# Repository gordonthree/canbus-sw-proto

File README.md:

# CAN bus switch prototype

Some circuit board sketches in the free version of EagleCad

## Brain board
* Raspberry Pi 3 or 4?
* Touchscreen usb + hdmi
* CAN bus to SPI shield
* Web based interface

## Alt brain board
* 1x ESP32
* 1x CAN bus transciever
* 1x 4-pos screw terminal for power + can
* 

## Demo 01 - Single switch with STM32 and CANBUS
* <br>
* 1x STM32F042
* 1x Isolated CAN bus transciever
* 1x Infineon BTS50010-1TAD PROFet Smart High Side Switch
* Voltage monitoring via resistor divider
* Current monitoring via Smart Switch
* Onboard 3v3 and 5v linear regulators
* Headers for SWLINK and UART
* Wago style screw terminal connector for 2-wire + drain CANBUS cable
* High current terminal block style battery input and load output
  
## Demo 02 - Single switch 
* 1x Infineon BTS50010-1TAD PROFet Smart High Side Switch
* Voltage monitoring via resistor divider
* Current monitoring via Smart Switch
* Header for control connection to microcontroller
* High current terminal block style battery input and load output

## Demo 03 - Dual switch with STM32 and CANBUS
* 1x STM32F042
* 1x Isolated CAN bus transciever
* 2x Infineon BTS50010-1TAD PROFet Smart High Side Switch
* Voltage monitoring via resistor divider
* Current monitoring via Smart Switch
* Onboard 3v3 and 5v linear regulators
* Headers for SWLINK and UART
* Wago style screw terminal connector for 2-wire + drain CANBUS cable
* High current terminal block style battery input and load output
  
## Prototype 01 Four switches
* 1x ESP32
* 1x CAN bus transciever
* 2x p-channel FETs (20a max?)
* 2x high side switch ICs (10a max?)
* 1x dual chan driver TC4472
* 1x 6-pos barrier strip V+ GND SW1 SW2 SW3 SW4
* 1x 3-pos terminal for can bus
* 1x serial programming header

## Prototype 02 Three switches
* 1x ESP32
* 1x CAN bus transciever
* 2x p-channel FETs (30a max?) power-so8
* 1x high side switch ICs (10a max?)
* 1x dual chan driver TC4472
* 1x 6-pos barrier strip V+ V+ SW1 SW2 SW3 GND
* 1x 3-pos terminal for can bus
* 1x serial programming header
  
## Prototype 03 Six switch
* 1x ESP32
* 1x CAN bus transciever
* 4x p-channel FETs (30a max?) power-so8
* 2x high side switch ICs (10a max?)
* 1x dual chan driver TC4472
* 1x 3-pos barrier strip for power +12 +12 GND
* 2x 6-pos barrier strip SW1 GND SW2 GND SW3 GND - repeated for other side
* 1x 3-pos terminal for can bus
* 1x serial programming header

## Prototype 04 Three switches with STM32
* 1x STM32F042C6
* 1x CAN bus transciever
* 2x p-channel FETs (30a max?) power-so8
* 1x high side switch ICs (10a max?)
* 1x dual chan driver TC4472
* 1x 6-pos barrier strip V+ V+ SW1 SW2 SW3 GND
* 1x 3-pos terminal for can bus
* 1x serial programming header
 
## Minimum interconnect for nodes
* 2-pair cable with drain
* first pair for CANH-IN and CANL-IN
* second pair for CANH-OUT and CANL-OUT
* drain is grounded at controller / hub

## Ideal interconnect for nodes
* 4-pair cable with drain
* first pair for CANH-IN and CANL-IN
* second and fourth pair for +VBAT and ground
* third pair for CANH-OUT and CANL-OUT
* drain is grounded at controller / hub

## CAN Hub
* eight total de9 connectors, one input, one output, six spurs
* each spur is wired in series, with Cx-IN and Cx-OUT daisy chained
* spurs that are not connected have a shorting plug installed connecting Cx-IN to Cx-OUT

## Parts
* 4x8 RGB matrix keypad https://www.adafruit.com/product/4020
* high side switch (ssr) https://mou.sr/4jcK616
* 6 position terminal block https://mou.sr/4i4P92Y
* heavy duty 6-pos terminal https://mou.sr/3R63QYn
* heavy duty 3-pos terminal block https://mou.sr/3FTFHBW
* ATO fuse holder https://mou.sr/4cihwsZ
* CANBUS Transceiver MCP2562T https://mou.sr/4llTLVa 
* ESP32 Module https://mou.sr/4j1XWDP
* Onboard DC-DC converter https://mou.sr/4i8eVTN
* P chan fet chonky https://mou.sr/42aUOja
* P chan power-so8 https://mou.sr/42BhcBs
* 3.3v LDO regulator https://mou.sr/3RgIUy6
* 20 awg shielded twisted pair cable https://a.co/d/8FQRYBL
* Texas Inst mosfet driver 5a inverted dual-ch SO8 https://mou.sr/3YqDYuk
* STM32 Micro with CAN bus 20 pin ssop https://mou.sr/4jwf9Fx
* ESP32 WROOM module with antenna https://mou.sr/3XWw2kl
* STM32 Dev Board using inexepensive mcu https://www.digikey.com/short/59jq87v5
* STM32 48-pin QFP STM32F042C6T7 https://mou.sr/3Eqjfjx
* DC-DC Switching regulator TPS560430 automotive 5v output https://mou.sr/4cZ1YLn
* DC-DC Sync-switching regulator LMR51625 automotive adjustable output https://mou.sr/4ipTHB4

## remote node introductions
* 10 seconds after boot remote nodes will start sending introduction messages 0x7XX
  * master will record message id and node id for each device
  * master will compare node id with database of known nodes
  * nodes that are already known will have their last-seen timestamp updated
  * newly introduced nodes will be added to the database, recording their first-seen timestamp
  * master will respond with 0x401 to the node to acknowledge introduction
  * after reciving 0x401 the remote node will clear the introduction flag and enter normal operation
* after no introductions the master will enumerate new nodes
  * master will send 0x402:0x40A to the remote node and nodes will respond with 0x710:0x74F for each module the node offers
  * modules will be recorded in database using unique 32-bit node ID and 16-bit module ID
  * master will send 0x401 to the remote node after recording each module 
* after introductions and enumeration master will review database of nodes
  * nodes with a timestamp older than the current boot timestamp will be marked as not-present
    * master will send 0x40C node check message to the node
    * if remote node responds with their node id, update last seen, flag for enumeration 
    * if remote node does not respond mark the node missing in the database and alert user

## normal operation
* after introduction and enumeration are complete master will send 0x10A indicating nodes should begin normal operation
* nodes start sending 0x5XX data messages at the configured rates

## request info flag
* master will instruct display module to request info, providing a message id
* display module will watch for the message id and receive 8 bytes of data

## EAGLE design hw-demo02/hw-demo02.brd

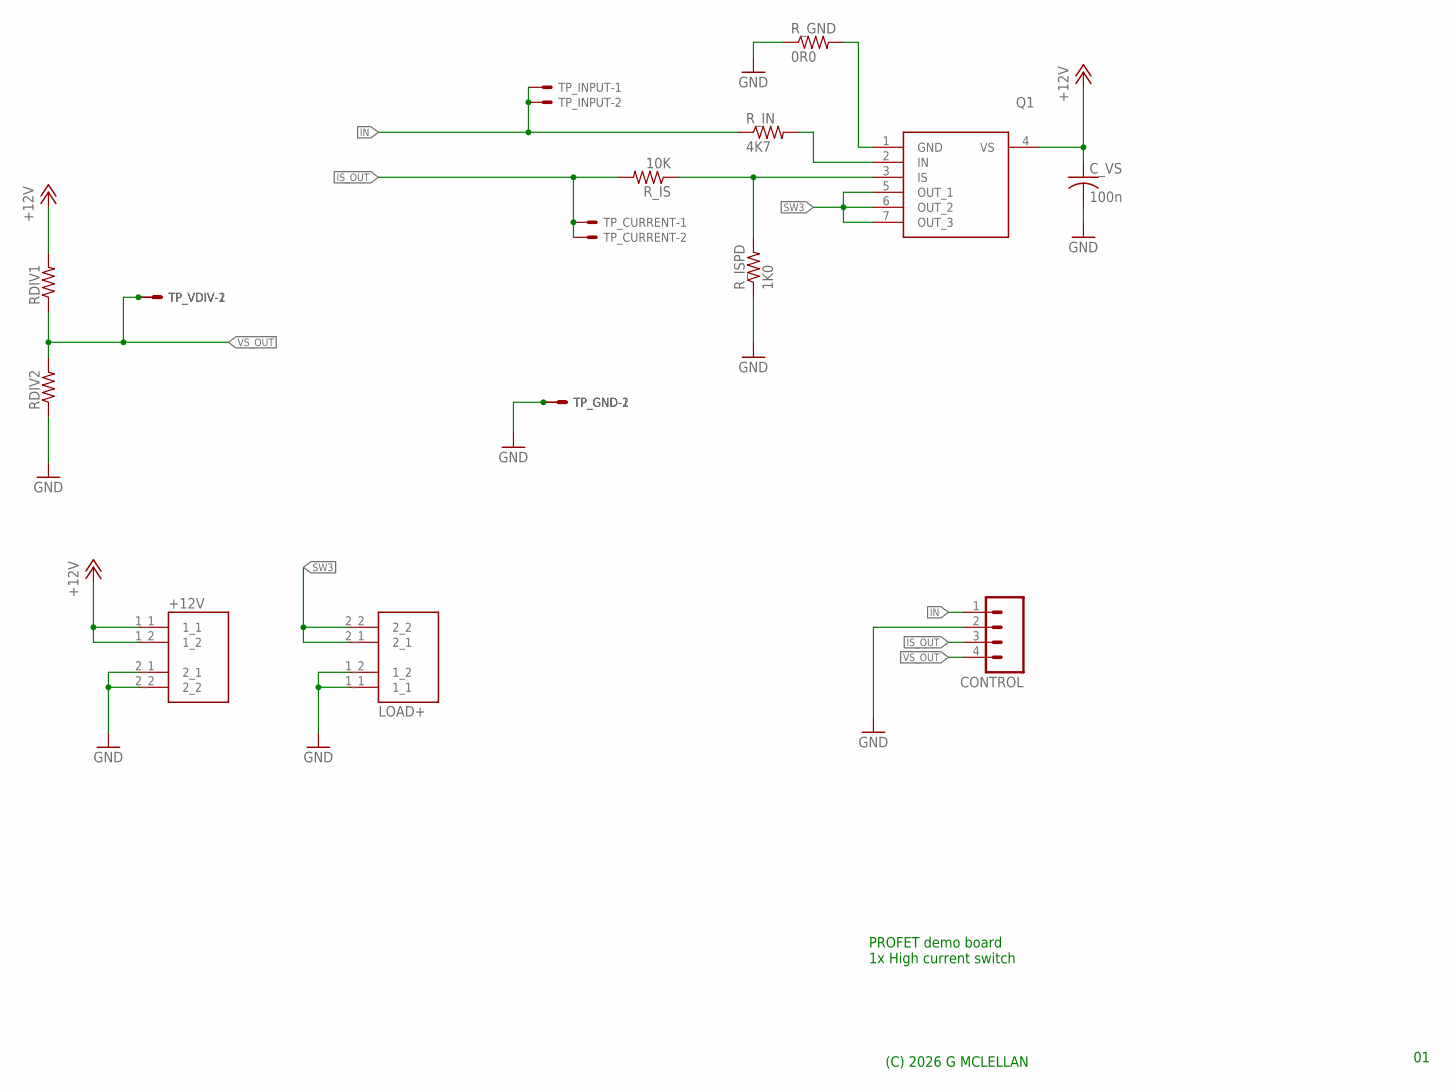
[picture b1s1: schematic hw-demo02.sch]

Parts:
+12V: VP0265840000G; AMPHENOL_VP0265840000G
CONTROL: M04LOCK; 1X04_LOCK
C_VS: 100n; C0805K
LOAD+: VP0265840000G; AMPHENOL_VP0265840000G
Q1: BTS500101TADATMA2
RDIV1, RDIV2: R-US_R0805; R0805
R_GND: 0R0; R1206W
R_IN: 4K7; 0207/12
R_IS: 10K; 0207/12
R_ISPD: 1K0; 0207/12
TP_CURRENT: 22-23-2021
TP_GND: 22-23-2021
TP_INPUT: 22-23-2021
TP_VDIV: 22-23-2021

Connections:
+12V: +12V.1_1, +12V.1_2, C_VS.1, Q1.4 (VS), RDIV1.2
CTL3`: Q1.2 (IN), R_IN.2
GND: +12V.2_1, +12V.2_2, CONTROL.2, C_VS.2, LOAD+.1_1, LOAD+.1_2, RDIV2.1, R_GND.1, R_ISPD.1, TP_GND.1, TP_GND.2
IN: CONTROL.1, R_IN.1, TP_INPUT.1, TP_INPUT.2
IS: Q1.3 (IS), R_IS.1, R_ISPD.2
IS_OUT: CONTROL.3, R_IS.2, TP_CURRENT.1, TP_CURRENT.2
unnamed: Q1.1 (GND), R_GND.2
SW3: LOAD+.2_1, LOAD+.2_2, Q1.5 (OUT_1), Q1.6 (OUT_2), Q1.7 (OUT_3)
VS_OUT: CONTROL.4, RDIV1.1, RDIV2.2, TP_VDIV.1, TP_VDIV.2

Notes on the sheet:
PROFET demo board 1x High current switch
(C) 2026 G MCLELLAN

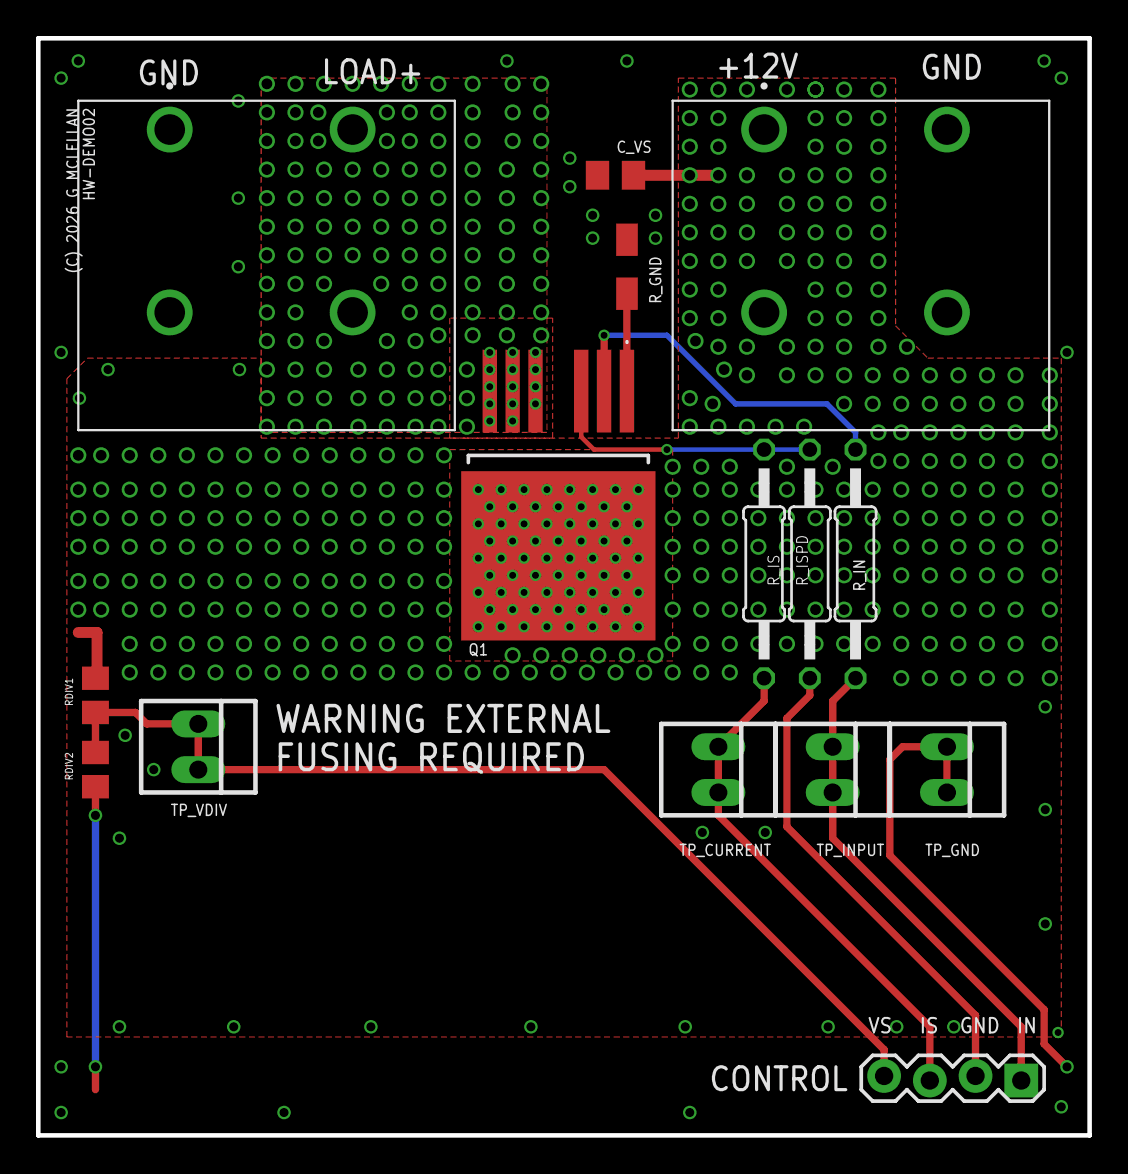
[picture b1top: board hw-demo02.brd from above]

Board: 2 copper layers, 58.4 x 61.0 mm, 15 parts (0 on the bottom side), 9 nets.

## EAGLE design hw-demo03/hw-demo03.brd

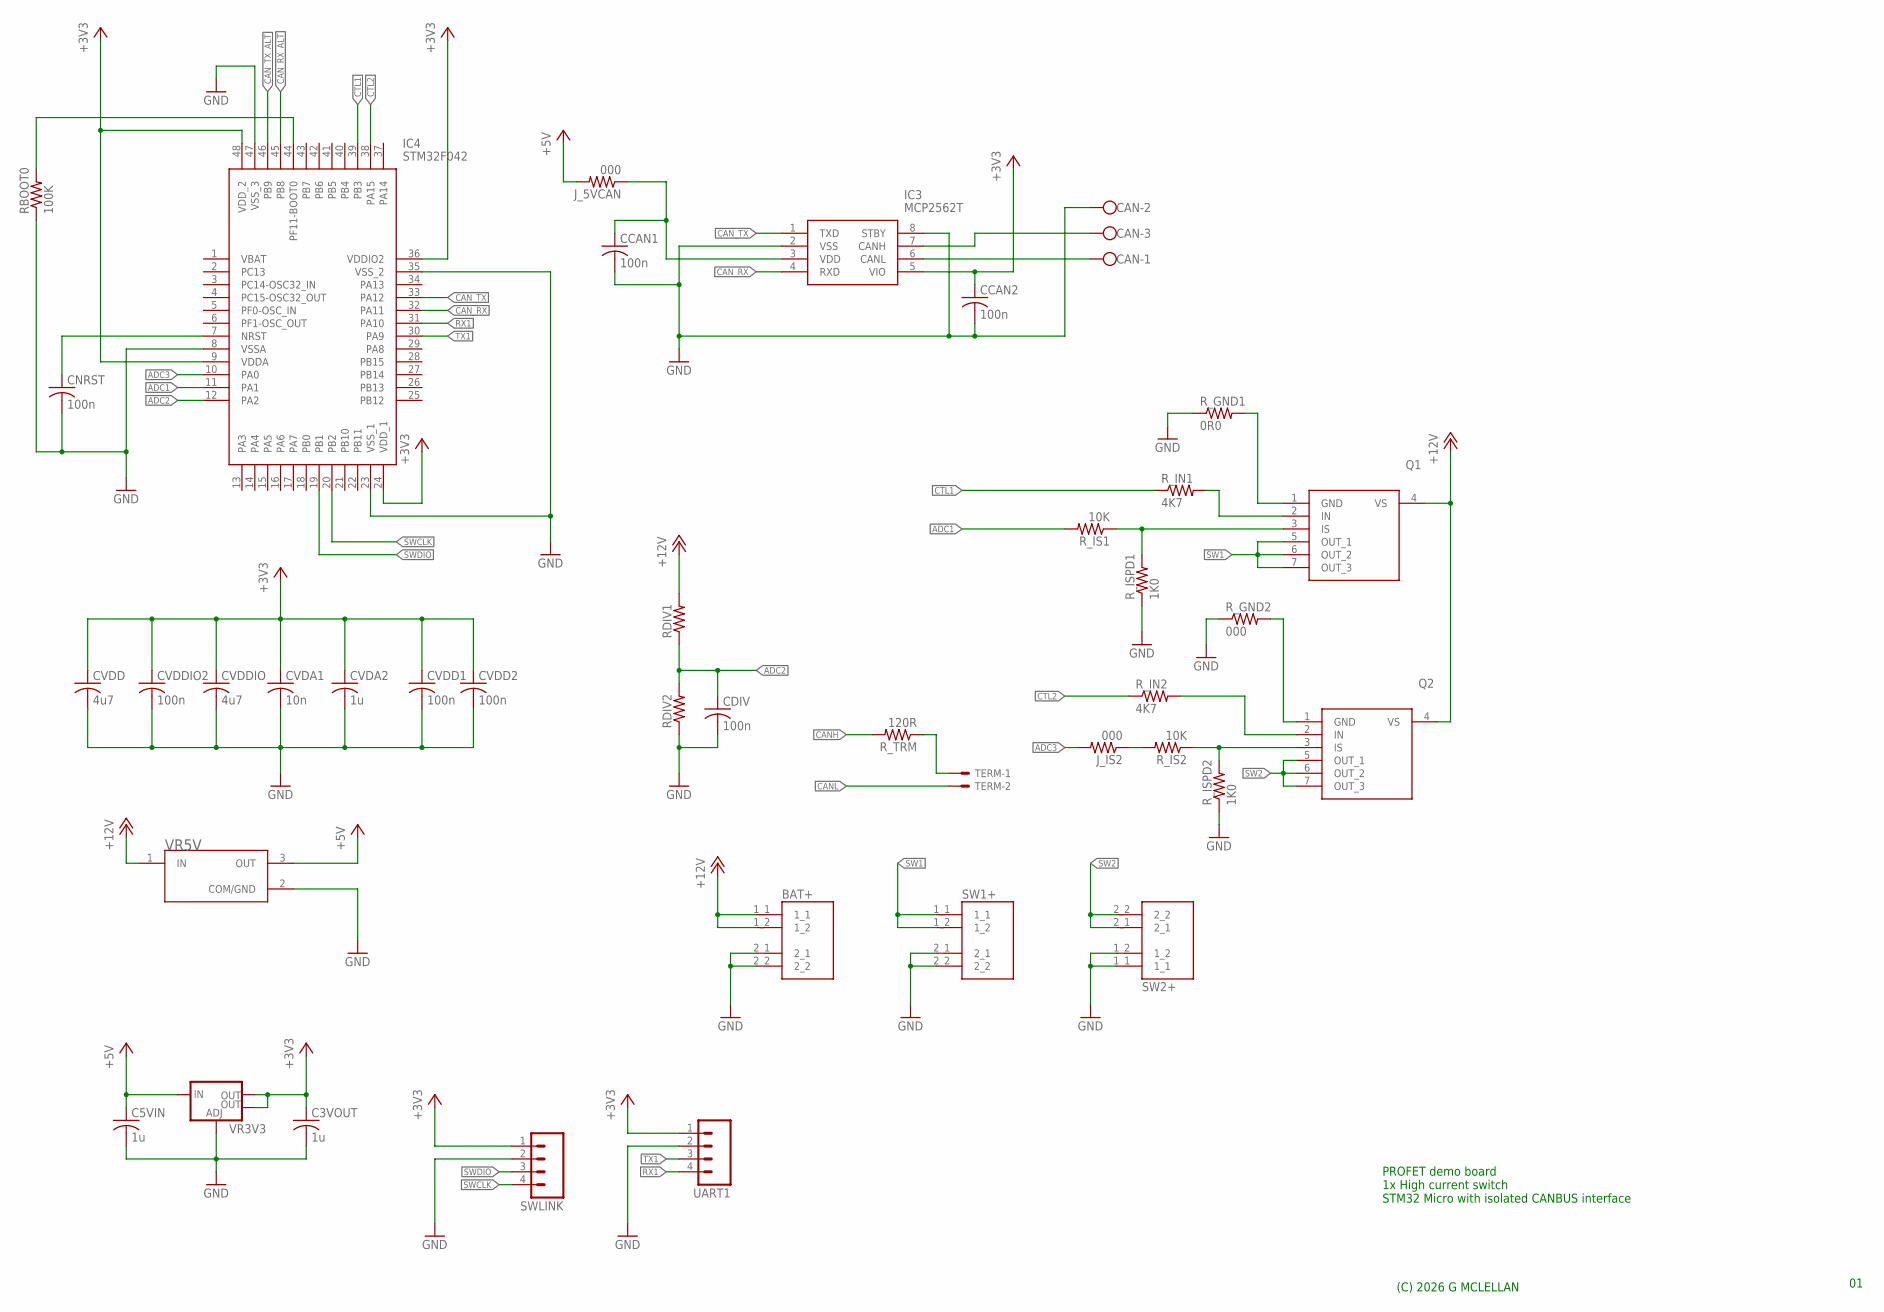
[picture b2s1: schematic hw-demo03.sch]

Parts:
BAT+: VP0265840000G; AMPHENOL_VP0265840000G
C3VOUT: 1u; C0805K
C5VIN: 1u; C1206K
CAN: W237-103
CCAN1, CCAN2: 100n; C0603K
CDIV: 100n; C0603K
CNRST: 100n; C0603K
CVDA1: 10n; C0603K
CVDA2: 1u; C0603K
CVDD: 4u7; C0603K
CVDD1, CVDD2: 100n; C0603K
CVDDIO: 4u7; C0603K
CVDDIO2: 100n; C0603K
IC3: MCP2562T; SOIC127P600X175-8N
IC4: STM32F042; QFP50P900X900X160-48N
J_5VCAN: 000; 0207/15
J_IS2: 000; 0207/15
Q1, Q2: BTS500101TADATMA2
RBOOT0: 100K; R0603
RDIV1, RDIV2: R-US_R0805; R0805
R_GND1: 0R0; R1206W
R_GND2: 000; R1206W
R_IN1: 4K7; 0207/10
R_IN2: 4K7; 0204/7
R_IS1, R_IS2: 10K; 0204/7
R_ISPD1, R_ISPD2: 1K0; 0204/7
R_TRM: 120R; 0204/7
SW1+, SW2+: VP0265840000G; AMPHENOL_VP0265840000G
SWLINK: M04LOCK; 1X04_LOCK
TERM: 22-23-2021
UART1: M04LOCK; 1X04_LOCK
VR3V3: V_REG_LM1117SOT223; SOT223
VR5V: OKI-78SR-5/1.5-W36-C; CONV_OKI-78SR-5/1.5-W36-C

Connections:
+3V3: C3VOUT.1, CCAN2.1, CVDA1.1, CVDA2.1, CVDD.1, CVDD1.1, CVDD2.1, CVDDIO.1, CVDDIO2.1, IC3.5 (VIO), IC4.9 (VDDA), IC4.24 (VDD_1), IC4.36 (VDDIO2), IC4.48 (VDD_2), SWLINK.1, UART1.1, VR3V3.2 (OUT), VR3V3.4 (OUT)
+5V: C5VIN.1, J_5VCAN.2, VR3V3.3 (IN), VR5V.3 (OUT)
+12V: BAT+.1_1, BAT+.1_2, Q1.4 (VS), Q2.4 (VS), RDIV1.2, VR5V.1 (IN)
ADC1: IC4.11 (PA1), R_IS1.2
ADC2: CDIV.1, IC4.12 (PA2), RDIV1.1, RDIV2.2
ADC3: IC4.10 (PA0), J_IS2.2
BOOT0: IC4.44 (PF11-BOOT0), RBOOT0.2
CANH: CAN.3, IC3.7 (CANH), R_TRM.2
CANL: CAN.1, IC3.6 (CANL), TERM.2
CAN_RX: IC3.4 (RXD), IC4.32 (PA11)
CAN_RX_ALT: IC4.45 (PB8)
CAN_TX: IC3.1 (TXD), IC4.33 (PA12)
CAN_TX_ALT: IC4.46 (PB9)
CTL1: IC4.39 (PB3), R_IN1.1
CTL2: IC4.38 (PA15), R_IN2.1
CTL3`: Q1.2 (IN), R_IN1.2
GND: BAT+.2_1, BAT+.2_2, C3VOUT.2, C5VIN.2, CAN.2, CCAN1.2, CCAN2.2, CDIV.2, CNRST.2, CVDA1.2, CVDA2.2, CVDD.2, CVDD1.2, CVDD2.2, CVDDIO.2, CVDDIO2.2, IC3.2 (VSS), IC3.8 (STBY), IC4.8 (VSSA), IC4.23 (VSS_1), IC4.35 (VSS_2), IC4.47 (VSS_3), RBOOT0.1, RDIV2.1, R_GND1.1, R_GND2.1, R_ISPD1.1, R_ISPD2.1, SW1+.2_1, SW1+.2_2, SW2+.1_1, SW2+.1_2, SWLINK.2, UART1.2, VR3V3.1 (ADJ), VR5V.2 (COM/GND)
IS: Q1.3 (IS), R_IS1.1, R_ISPD1.2
unnamed: R_TRM.1, TERM.1
unnamed: J_IS2.1, R_IS2.2
unnamed: Q1.1 (GND), R_GND1.2
unnamed: Q2.1 (GND), R_GND2.2
unnamed: Q2.2 (IN), R_IN2.2
unnamed: Q2.3 (IS), R_IS2.1, R_ISPD2.2
unnamed: CCAN1.1, IC3.3 (VDD), J_5VCAN.1
unnamed: CNRST.1, IC4.7 (NRST)
RX1: IC4.31 (PA10), UART1.4
SW1: Q1.5 (OUT_1), Q1.6 (OUT_2), Q1.7 (OUT_3), SW1+.1_1, SW1+.1_2
SW2: Q2.5 (OUT_1), Q2.6 (OUT_2), Q2.7 (OUT_3), SW2+.2_1, SW2+.2_2
SWCLK: IC4.20 (PB2), SWLINK.4
SWDIO: IC4.19 (PB1), SWLINK.3
TX1: IC4.30 (PA9), UART1.3

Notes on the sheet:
PROFET demo board 1x High current switch STM32 Micro with isolated CANBUS interface
(C) 2026 G MCLELLAN

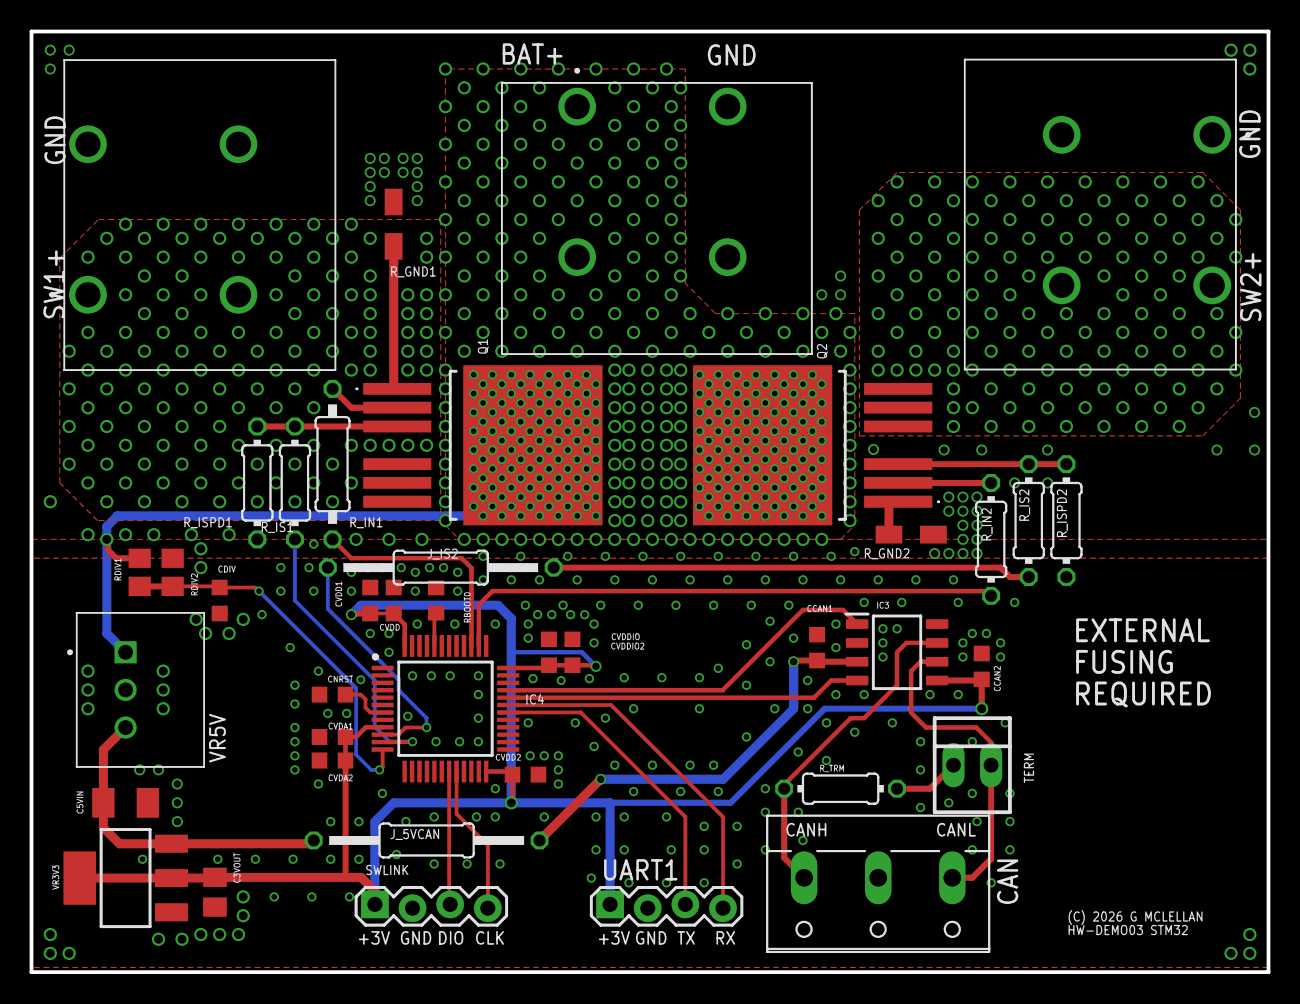
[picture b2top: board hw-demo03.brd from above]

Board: 2 copper layers, 83.5 x 63.5 mm, 40 parts (0 on the bottom side), 30 nets.

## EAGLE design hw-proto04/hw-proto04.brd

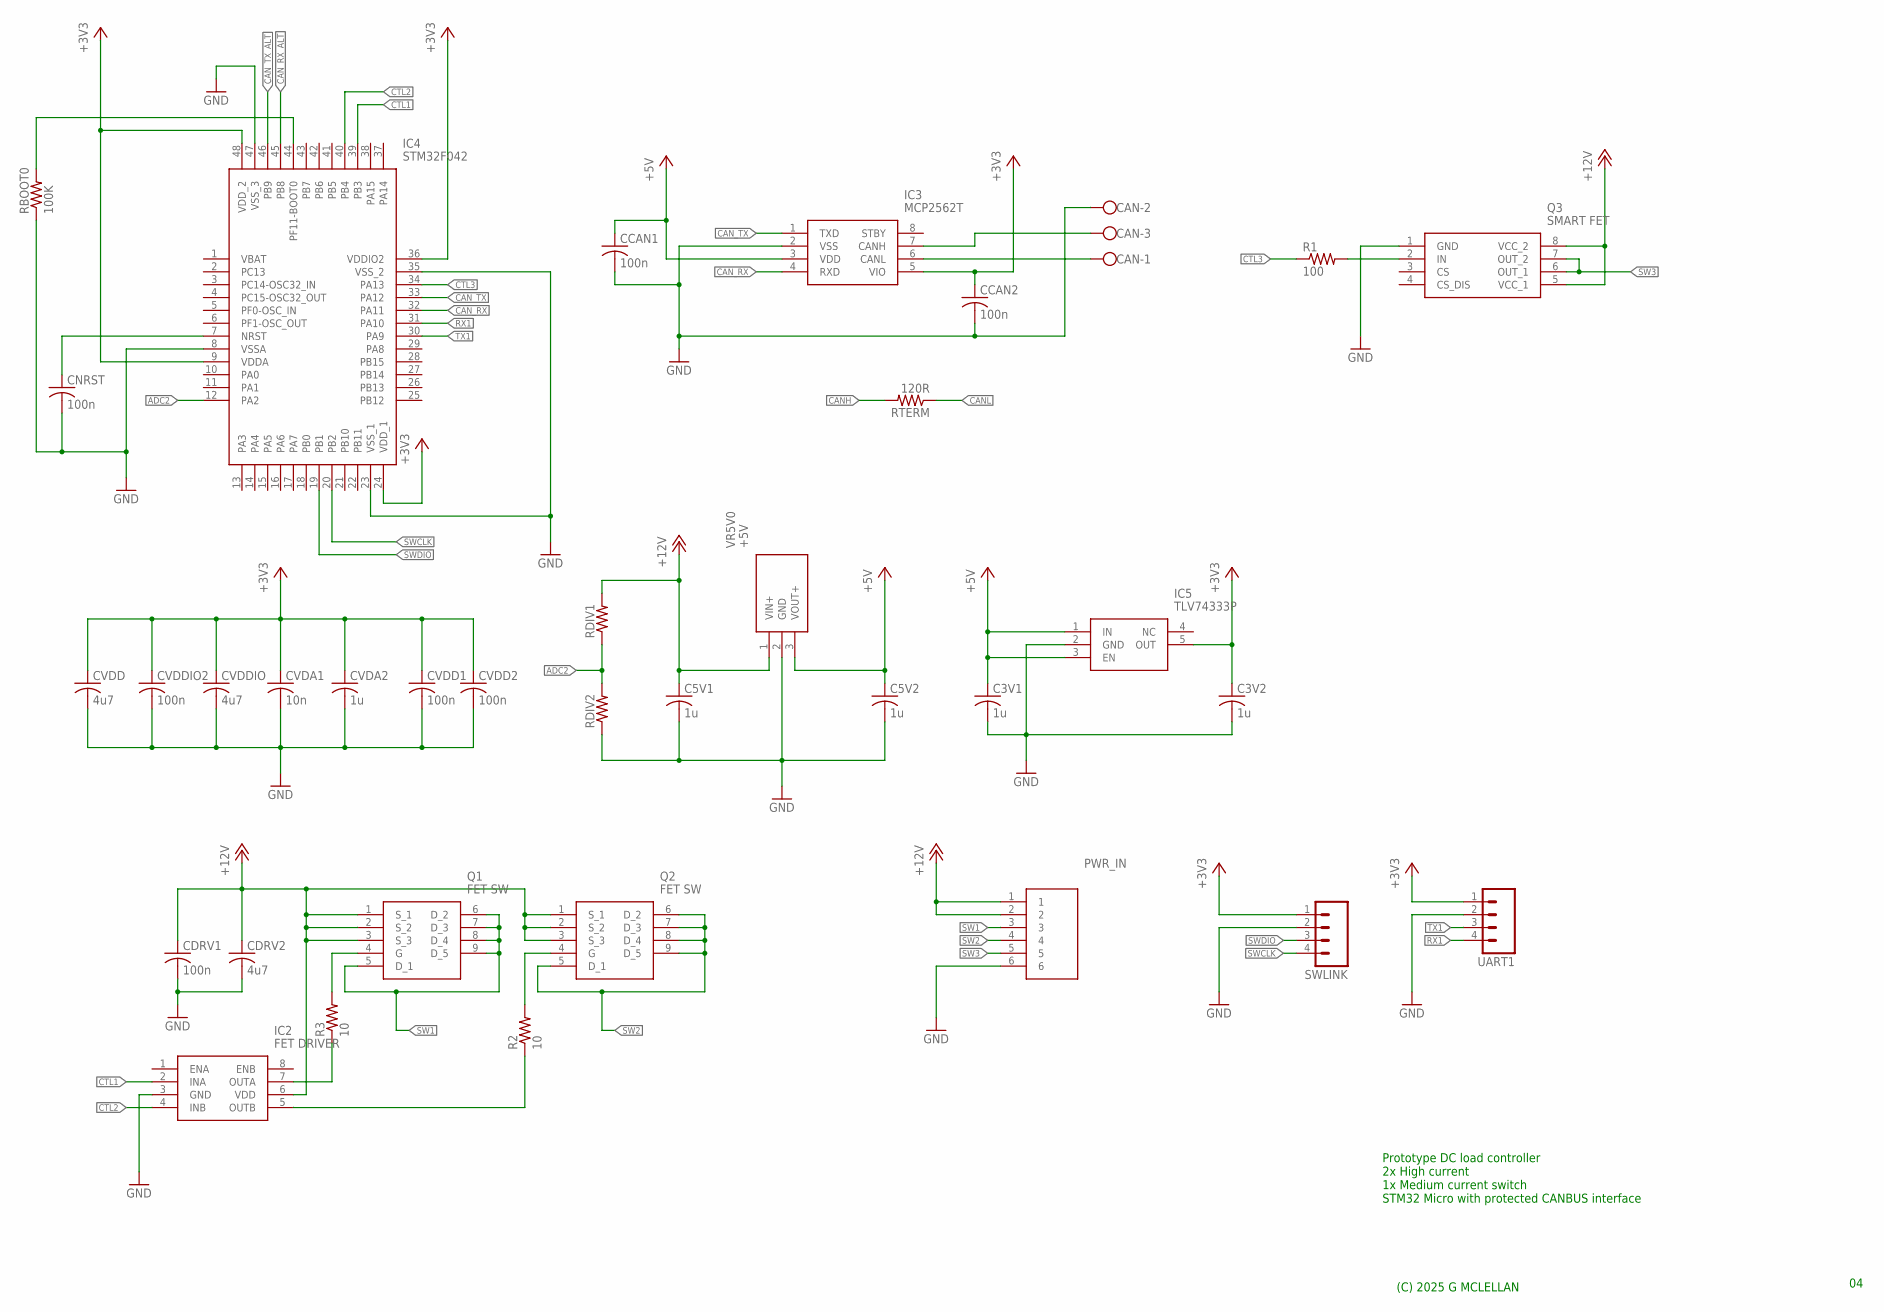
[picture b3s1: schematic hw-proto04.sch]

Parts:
C3V1, C3V2, C5V1, C5V2: 1u; C0603K
CAN: W237-103
CCAN1, CCAN2: 100n; C0603K
CDRV1: 100n; C0603K
CDRV2: 4u7; C0805K
CNRST: 100n; C0603K
CVDA1: 10n; C0603K
CVDA2: 1u; C0603K
CVDD: 4u7; C0603K
CVDD1, CVDD2: 100n; C0603K
CVDDIO: 4u7; C0603K
CVDDIO2: 100n; C0603K
IC2: FET DRIVER; SOIC127P600X175-8N
IC3: MCP2562T; SOIC127P600X175-8N
IC4: STM32F042; QFP50P900X900X160-48N
IC5: TLV74333P; SOT95P280X145-5N
PWR_IN: 4DB-P108-06; 4DBP10806
Q1, Q2: FET SW; SQJ147ELPT1_GE3
Q3: SMART FET; SOIC127P600X175-8N
R1: 100; 0204/7
R2, R3: 10; 0204/7
RBOOT0: 100K; R0603
RDIV1, RDIV2: R-US_R0805; R0805
RTERM: 120R; R0805
SWLINK: M04LOCK; 1X04_LOCK
UART1: M04LOCK; 1X04_LOCK
VR5V0: +5V; TSR-1-2433

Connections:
+3V3: C3V2.1, CCAN2.1, CVDA1.1, CVDA2.1, CVDD.1, CVDD1.1, CVDD2.1, CVDDIO.1, CVDDIO2.1, IC3.5 (VIO), IC4.9 (VDDA), IC4.24 (VDD_1), IC4.36 (VDDIO2), IC4.48 (VDD_2), IC5.5 (OUT), SWLINK.1, UART1.1
+5V: C3V1.1, C5V2.1, CCAN1.1, IC3.3 (VDD), IC5.1 (IN), IC5.3 (EN), VR5V0.3 (VOUT+)
+12V: C5V1.1, CDRV1.1, CDRV2.1, IC2.6 (VDD), PWR_IN.1, PWR_IN.2, Q1.1 (S_1), Q1.2 (S_2), Q1.3 (S_3), Q2.1 (S_1), Q2.2 (S_2), Q2.3 (S_3), Q3.5 (VCC_1), Q3.8 (VCC_2), RDIV1.2, VR5V0.1 (VIN+)
ADC2: IC4.12 (PA2), RDIV1.1, RDIV2.2
BOOT0: IC4.44 (PF11-BOOT0), RBOOT0.2
CANH: CAN.3, IC3.7 (CANH), RTERM.2
CANL: CAN.1, IC3.6 (CANL), RTERM.1
CAN_RX: IC3.4 (RXD), IC4.32 (PA11)
CAN_RX_ALT: IC4.45 (PB8)
CAN_TX: IC3.1 (TXD), IC4.33 (PA12)
CAN_TX_ALT: IC4.46 (PB9)
CTL1: IC2.2 (INA), IC4.39 (PB3)
CTL2: IC2.4 (INB), IC4.40 (PB4)
CTL3: IC4.34 (PA13), R1.1
GND: C3V1.2, C3V2.2, C5V1.2, C5V2.2, CAN.2, CCAN1.2, CCAN2.2, CDRV1.2, CDRV2.2, CNRST.2, CVDA1.2, CVDA2.2, CVDD.2, CVDD1.2, CVDD2.2, CVDDIO.2, CVDDIO2.2, IC2.3 (GND), IC3.2 (VSS), IC4.8 (VSSA), IC4.23 (VSS_1), IC4.35 (VSS_2), IC4.47 (VSS_3), IC5.2 (GND), PWR_IN.6, Q3.1 (GND), RBOOT0.1, RDIV2.1, SWLINK.2, UART1.2, VR5V0.2 (GND)
unnamed: IC2.5 (OUTB), R2.1
unnamed: IC2.7 (OUTA), R3.1
unnamed: Q1.4 (G), R3.2
unnamed: Q2.4 (G), R2.2
unnamed: Q3.2 (IN), R1.2
unnamed: CNRST.1, IC4.7 (NRST)
RX1: IC4.31 (PA10), UART1.4
SW1: PWR_IN.3, Q1.5 (D_1), Q1.6 (D_2), Q1.7 (D_3), Q1.8 (D_4), Q1.9 (D_5)
SW2: PWR_IN.4, Q2.5 (D_1), Q2.6 (D_2), Q2.7 (D_3), Q2.8 (D_4), Q2.9 (D_5)
SW3: PWR_IN.5, Q3.6 (OUT_1), Q3.7 (OUT_2)
SWCLK: IC4.20 (PB2), SWLINK.4
SWDIO: IC4.19 (PB1), SWLINK.3
TX1: IC4.30 (PA9), UART1.3

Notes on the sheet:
Prototype DC load controller 2x High current 1x Medium current switch STM32 Micro with protected CANBUS interface
(C) 2025 G MCLELLAN

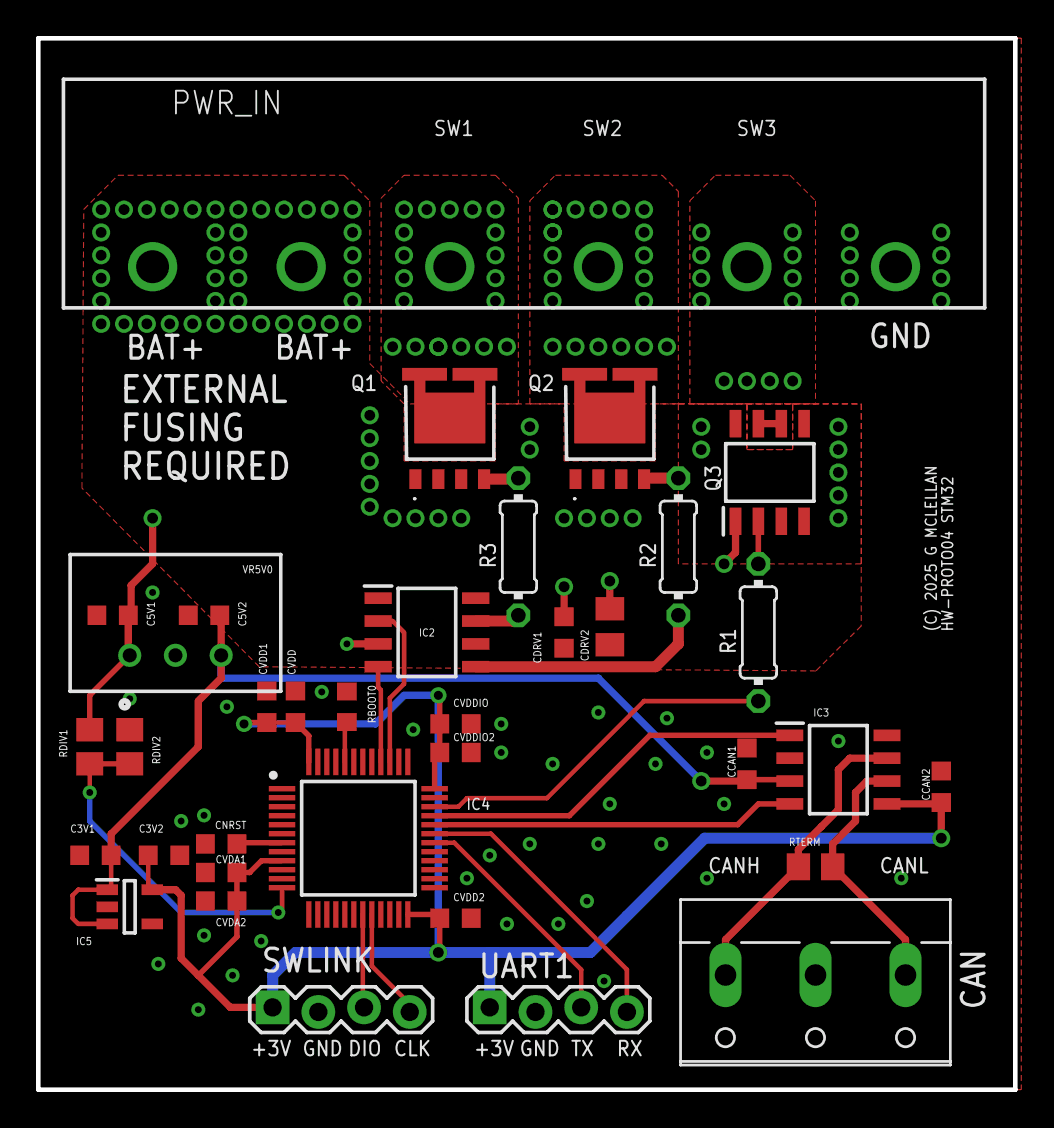
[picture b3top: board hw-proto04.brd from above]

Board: 2 copper layers, 54.3 x 58.4 mm, 35 parts (0 on the bottom side), 26 nets.

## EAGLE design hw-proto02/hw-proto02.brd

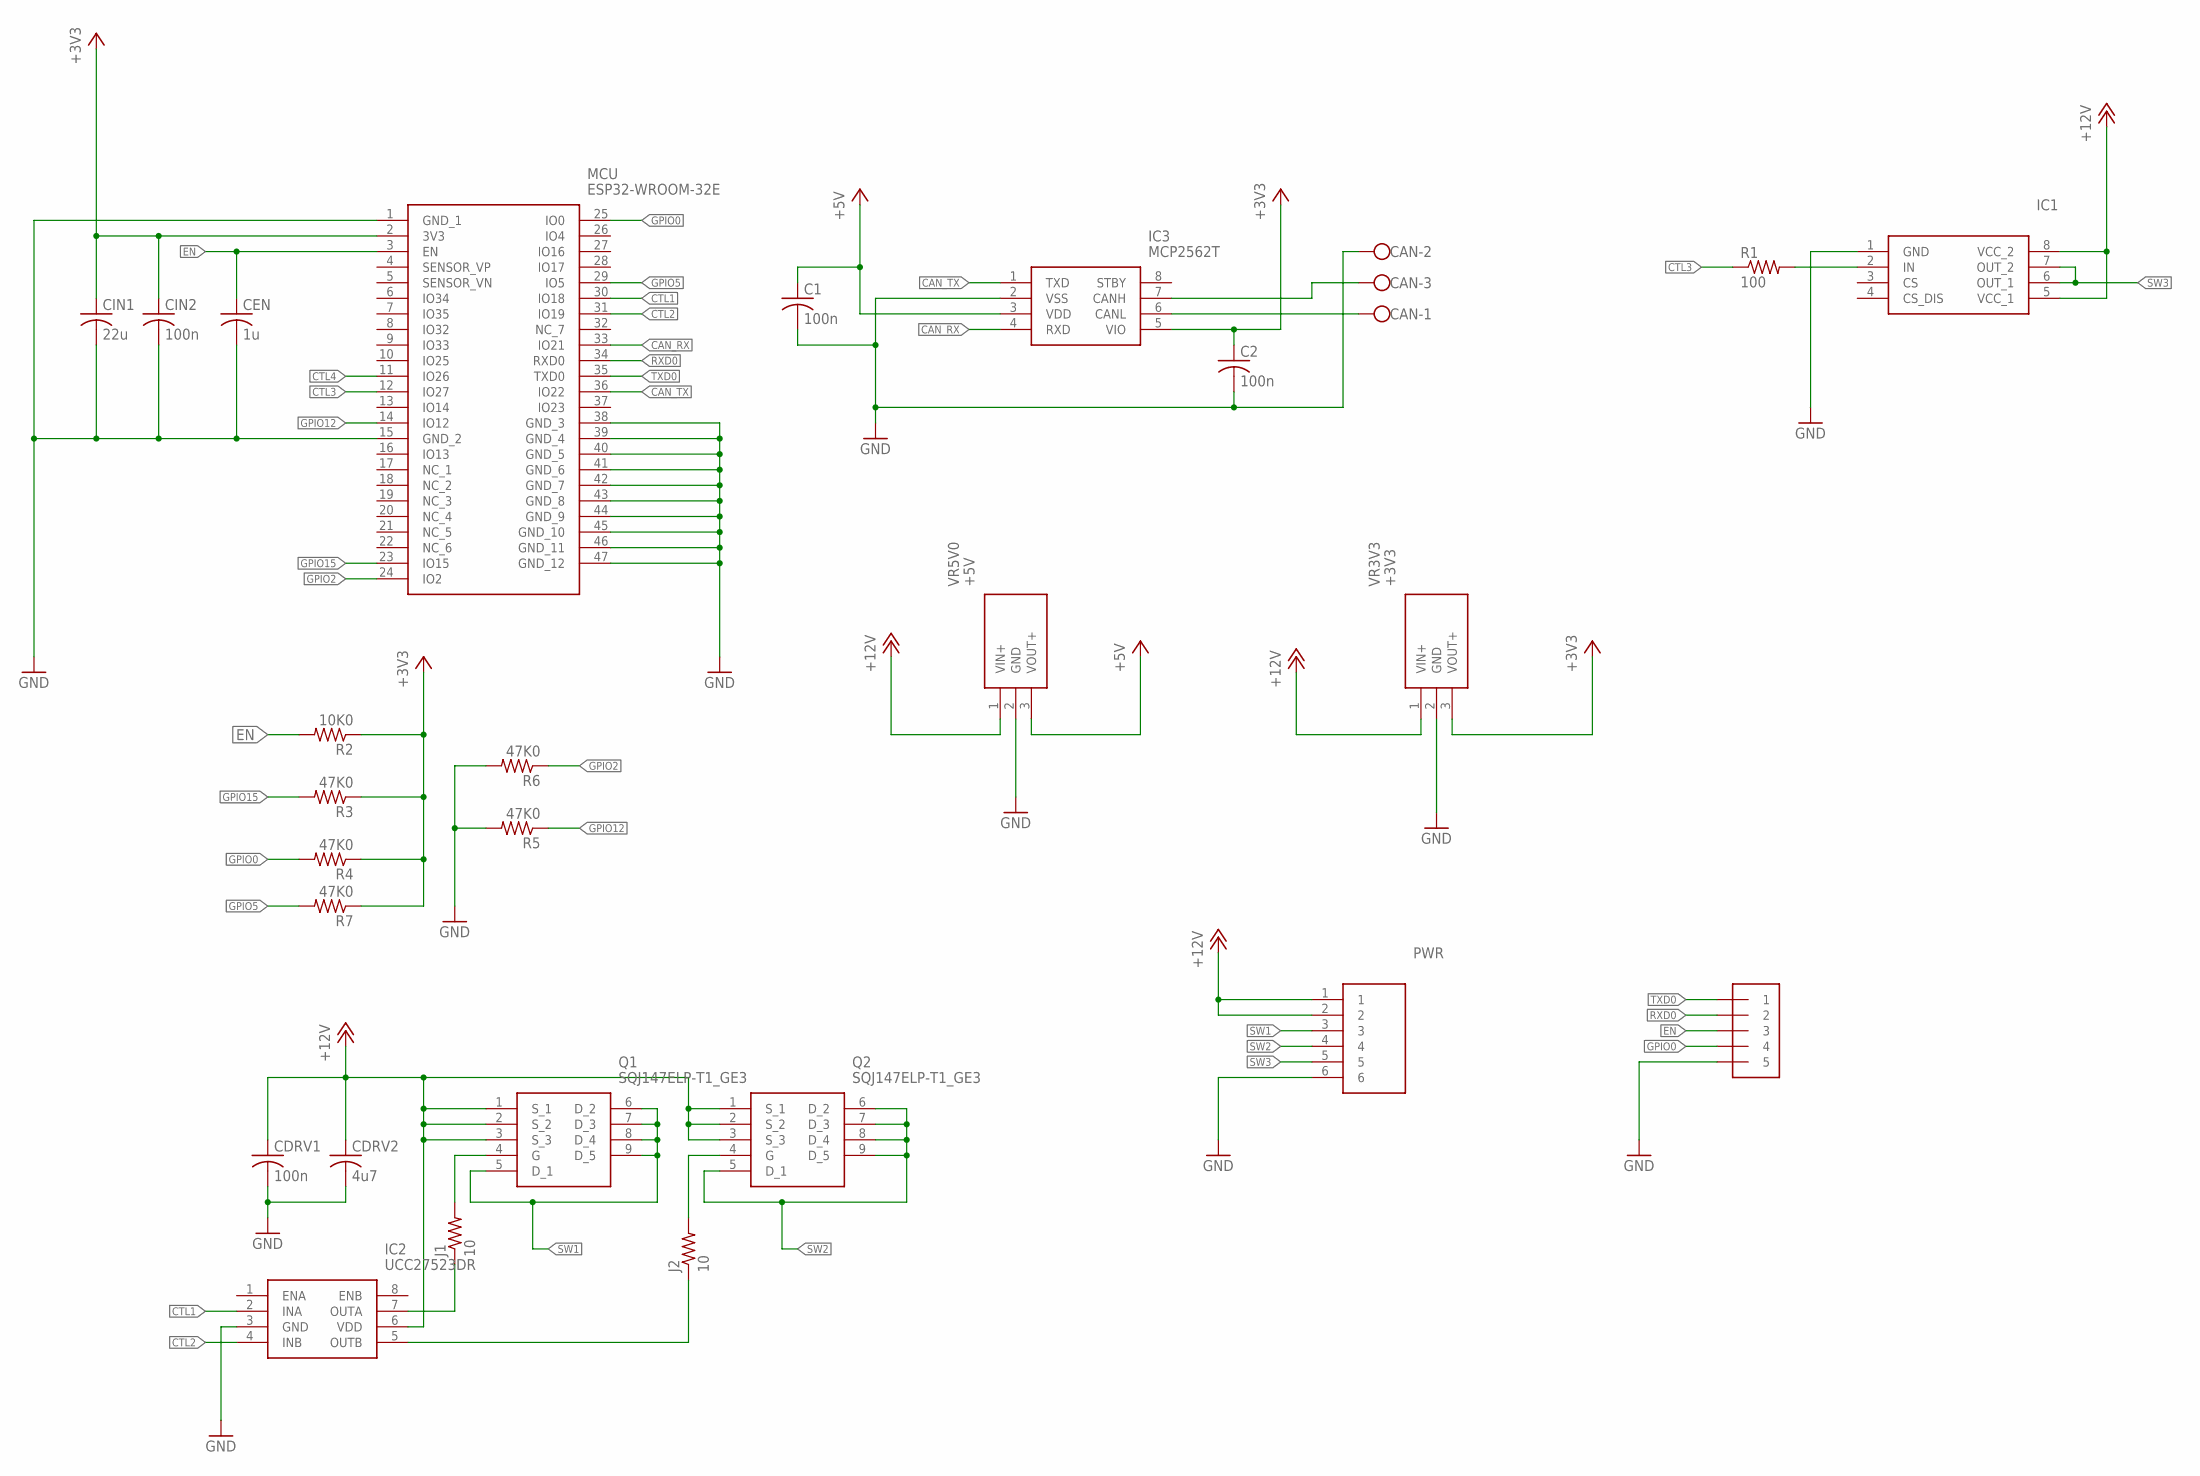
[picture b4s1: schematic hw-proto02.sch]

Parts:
C1, C2: 100n; C0603K
CAN: W237-103
CDRV1: 100n; C0603K
CDRV2: 4u7; C0805K
CEN: 1u; C0603K
CIN1: 22u; C0805K
CIN2: 100n; C0603K
IC1: VN5E160MSTR-E; SOIC127P600X175-8N
IC2: UCC27523DR; SOIC127P600X175-8N
IC3: MCP2562T; SOIC127P600X175-8N
J1, J2: 10; 0204/7
MCU: ESP32-WROOM-32E; ESP32WROOM32EN8R2
PROG: 1X5; 1X05-3.5MM
PWR: 4DB-P108-06; 4DBP10806
Q1, Q2: SQJ147ELP-T1_GE3; SQJ147ELPT1_GE3
R1: 100; 0204/7
R2: 10K0; R0603
R3, R4, R5, R6, R7: 47K0; R0603
VR3V3: +3V3; TSR-1-2433
VR5V0: +5V; TSR-1-2433

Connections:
+3V3: C2.1, CIN1.1, CIN2.1, IC3.5 (VIO), MCU.2 (3V3), R2.1, R3.1, R4.1, R7.1, VR3V3.3 (VOUT+)
+5V: C1.1, IC3.3 (VDD), VR5V0.3 (VOUT+)
+12V: CDRV1.1, CDRV2.1, IC1.5 (VCC_1), IC1.8 (VCC_2), IC2.6 (VDD), PWR.1, PWR.2, Q1.1 (S_1), Q1.2 (S_2), Q1.3 (S_3), Q2.1 (S_1), Q2.2 (S_2), Q2.3 (S_3), VR3V3.1 (VIN+), VR5V0.1 (VIN+)
CAN_RX: IC3.4 (RXD), MCU.33 (IO21)
CAN_TX: IC3.1 (TXD), MCU.36 (IO22)
CTL1: IC2.2 (INA), MCU.30 (IO18)
CTL2: IC2.4 (INB), MCU.31 (IO19)
CTL3: MCU.12 (IO27), R1.1
CTL4: MCU.11 (IO26)
EN: CEN.1, MCU.3 (EN), PROG.3, R2.2
GND: C1.2, C2.2, CAN.2, CDRV1.2, CDRV2.2, CEN.2, CIN1.2, CIN2.2, IC1.1 (GND), IC2.3 (GND), IC3.2 (VSS), MCU.1 (GND_1), MCU.15 (GND_2), MCU.38 (GND_3), MCU.39 (GND_4), MCU.40 (GND_5), MCU.41 (GND_6), MCU.42 (GND_7), MCU.43 (GND_8), MCU.44 (GND_9), MCU.45 (GND_10), MCU.46 (GND_11), MCU.47 (GND_12), PROG.5, PWR.6, R5.2, R6.2, VR3V3.2 (GND), VR5V0.2 (GND)
GPIO0: MCU.25 (IO0), PROG.4, R4.2
GPIO2: MCU.24 (IO2), R6.1
GPIO5: MCU.29 (IO5), R7.2
GPIO12: MCU.14 (IO12), R5.1
GPIO15: MCU.23 (IO15), R3.2
unnamed: CAN.3, IC3.7 (CANH)
unnamed: CAN.1, IC3.6 (CANL)
unnamed: IC2.5 (OUTB), J2.1
unnamed: IC2.7 (OUTA), J1.1
unnamed: J1.2, Q1.4 (G)
unnamed: J2.2, Q2.4 (G)
unnamed: IC1.2 (IN), R1.2
RXD0: MCU.34 (RXD0), PROG.2
SW1: PWR.3, Q1.5 (D_1), Q1.6 (D_2), Q1.7 (D_3), Q1.8 (D_4), Q1.9 (D_5)
SW2: PWR.4, Q2.5 (D_1), Q2.6 (D_2), Q2.7 (D_3), Q2.8 (D_4), Q2.9 (D_5)
SW3: IC1.6 (OUT_1), IC1.7 (OUT_2), PWR.5
TXD0: MCU.35 (TXD0), PROG.1

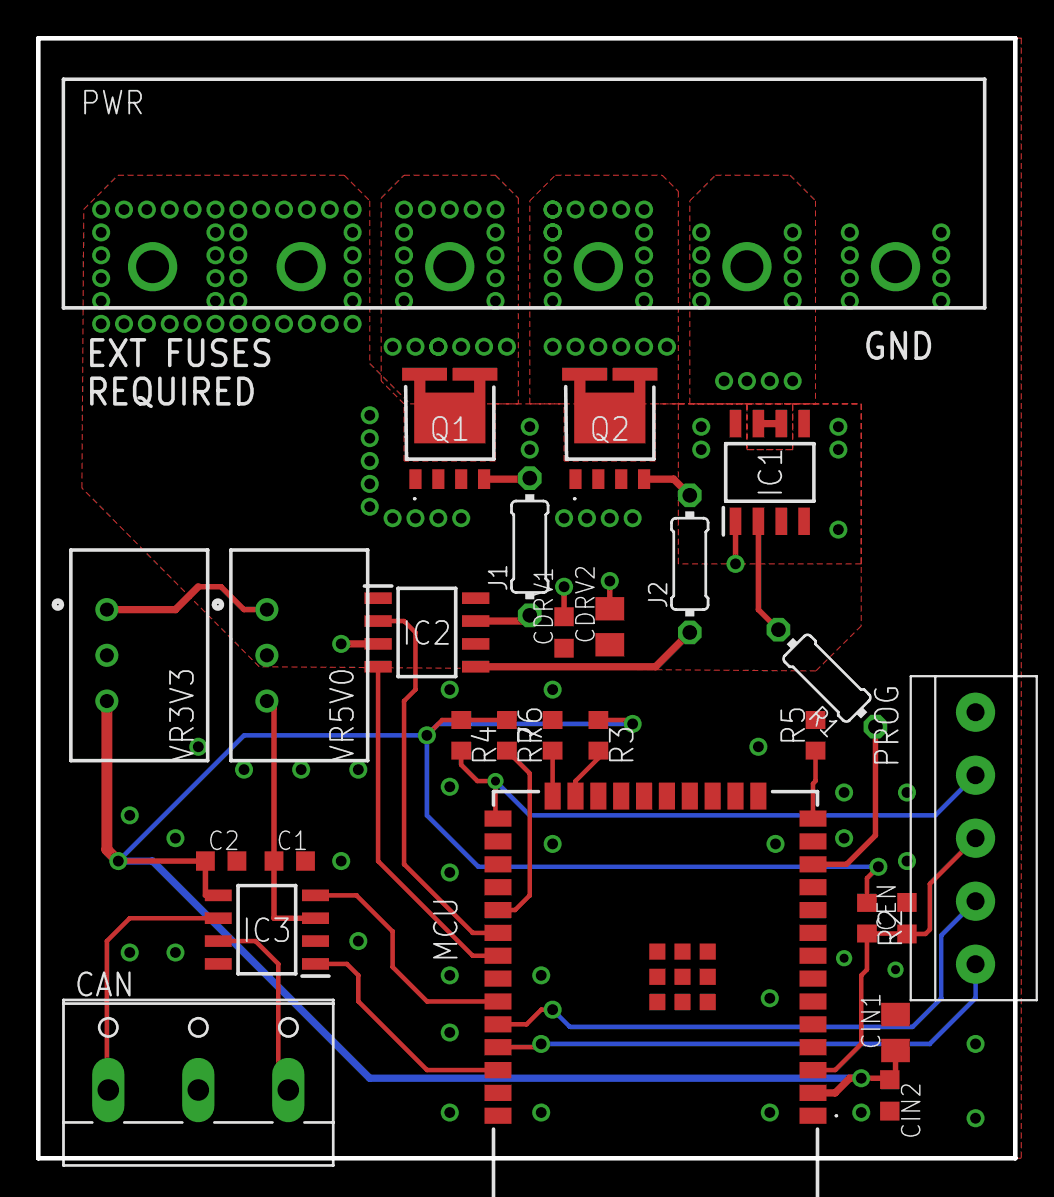
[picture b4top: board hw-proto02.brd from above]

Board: 2 copper layers, 54.3 x 62.2 mm, 27 parts (0 on the bottom side), 27 nets.

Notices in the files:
parts and their libraries:
SparkFun-Connectors: Licensing: Creative Commons ShareAlike 4.0 International - https://creativecommons.org/licenses/by-sa/4.0
